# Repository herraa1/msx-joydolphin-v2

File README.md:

# Nintendo Gamecube controller adapter for MSX (msx-joydolphin) v2

Connect [Nintendo Gamecube controllers](https://en.wikipedia.org/wiki/GameCube_controller) to [MSX computers](https://www.msx.org/wiki/).

> [!NOTE]
>
> No build instructions are yet provided, but if you are brave enough go for the [recommended build](#recommended-build).
>

## Introduction

The msx-joydolphin v2 is an adapter that allows connecting Nintendo Gamecube controllers to [MSX general purpose I/O ports](https://www.msx.org/wiki/General_Purpose_port).

The main features of the msx-joydolphin v2 adapter are:
* small footprint
* made of widely available electronic components
* behaves as a cord extension between the MSX computer and the Nintendo Gamecube controller
* uses a female standard DE9 connector on the adapter's MSX joystick side
* uses a Gamecube Controller socket on the adapter's Nintendo Gamecube controller side
* no need for external power supply for wired controllers, the adapter draws current from the MSX port
* low power consumption for wired controllers (<20mA)
* serial debug provides information about the operation of the adapter
* supports WaveBird Wireless Controllers (which draw up to 150mA) when powering the adapter via USB

## Changes since v1

The msx-joydolphin v2 adapter now follows the behavior of the MSX joystick reference diagram of the MSX Technical Databook,
even when pin8 of the MSX general purpose I/O port is HIGH.
This makes the adapter now work seamlessly with MSX-HID, which required entering FM Towns compatibility mode
in msx-joydolphin v1.

## Adapter Name

Why msx-joydolphin?
The first part of the name is pretty obvious: _"msx"_ as this is an adapter for MSX computers and _"joy"_ as this is a joystick adapter.
The _"dolphin"_ part comes from the project codename assigned to the Nintendo Gamecube during its development.

## [Hardware](hardware/kicad/)

The msx-joydolphin v2 adapter uses an [Arduino Nano](https://store.arduino.cc/products/arduino-nano) to convert the [Nintendo Gamecube controller signalling](http://www.int03.co.uk/crema/hardware/gamecube/gc-control.html) to the [MSX joystick standard signalling](https://www.msx.org/wiki/Joystick_control).

A small printed circuit board (PCB) is used to easily bind all components:
* The Arduino Nano is connected using female headers (or soldered directly, when using the proposed the plastic case)
* PH2.0 connectors are used to connect cable extensions
* A 2.54 pitch debug header is added for convenience
* Through-hole components are used on the front side
* Surface mount device (SMD) components are used on the back side
  * The SMD components use footprints and sizes (1206) to make hand-soldering easier

Connection to the MSX general purpose I/O port is implemented using a DE9 joystick extension cable with a female DE9 connector on one side and a loose end on the other side.
The MSX joystick extension cable loose end is wired according to the following pinout mapping.

|  |
|:--|
| MSX joystick connector pinout, from controller plug side |

| MSX side pin | Cable color (may vary) | Signal | Arduino Nano side (port/pin/number) |
| ------------ | ---------------------- | ------ | ----------------------------------- |
| 5            | Brown                  | +5v    | _/5V/27                             |
| 4            | Orange                 | RIGHT  | PB3/D11/14                          |
| 3            | Grey                   | LEFT   | PB2/D10/13                          |
| 2            | Black                  | DOWN   | PB1/D9/12                           |
| 1            | Red                    | UP     | PB0/D8/11                           |
| 6            | Green                  | TRIGA  | PB4/D12/15                          |
| 7            | White                  | TRIGB  | PB5/D13/16                          |
| 8            | Blue                   | OUT    | PD2/D2/5                            |
| 9            | Yellow                 | GND    | _/GND/4,29                          |

The msx-joydolphin-v2 is fully compatible with MSX joysticks and honors the pin8 (OUT) signal.

The adapter uses open collector outputs (using 74LS03 Quad 2-Input NAND gates with open collector outputs) which makes the adapter safer [^3] than the
standard MSX joystick schematic depicted in the MSX Technical Data Book, as it avoids a series of undesired conditions that can lead to bus contention/short circuits.

Power is drawn from the +5V signal of the MSX general purpose I/O port, which is capable of delivering up to 50mA [^1].
The msx-joydolphin v2 draws below 20mA from the port when a wired controller is connected, so it is on the safe side. Anyway, the msx-joydolphin adapter uses a Positive Temperature Coeficient (PTC) resettable fuse of 50mA (F1) to limit current in case something goes wrong.

Also on the power side, a [1N5817 Schottky diode](https://www.onsemi.com/download/data-sheet/pdf/1n5817-d.pdf) (D1) is used to avoid leaking current from the msx-joydolphin adapter to the MSX in case the USB port of the Arduino Nano is connected to a computer or power supply while the adapter is plugged into an MSX.

Connection to the Nintendo Gamecube controller is done via a Nintendo Gamecube controller extension cable with a controller socket on one side and a loose end on the other side.
The Nintendo Gamecube controller extension cable loose end is wired according to the following pinout mapping.

|  |
|:--|
| Nintendo Gamecube connector pinout, from Nintendo Gamecube side |

| Gamecube socket pin | Cable color official | Cable color actual (may vary) | Signal | Comment                                                                   | Arduino Nano side (port/pin/number) |
| ------------------- | ---------------------| ----------------------------- | ------ | ------------------------------------------------------------------------- | ----------------------------------- |
| 1                   | Yellow               | White                         | +5v    | rumble, not used                                                          | N/C                                 |
| 2                   | Red                  | Red                           | DAT    | data line, uses 3v3 logic so it connects via a level shifter to PD7/D7/10 | \*( PD7/D7/10 )                     |
| 3                   | Green                | Black                         | GND    | ground                                                                    | _/GND/4,29                          |
| 4                   | White                | Blue                          | GND    | ground                                                                    | _/GND/4,29                          |
| 5                   |                      |                               |        |                                                                           | N/C                                 |
| 6                   | Blue                 | Green                         | 3.43v  | power line, 3v3                                                           | _/3v3/17                            |
| 7                   | Black                | N/A                           | GND    | ground                                                                    | N/C                                 |

The Nintendo Gamecube controller uses 3.3V for power and logic, except for the rumble motor which uses 5V.

Power for the Nintendo Gamecube controller is provided by the 3.3V pin of the FT232RL integrated in the Arduino Nano, which is capable of delivering up to 50mA [^2], enough to power a wired game controller.

As the Arduino Nano is a 5V logic microcontroller, the msx-joydolphin adapter uses a voltage level shifter based on the [BSS138 N-Channel Logic Level Enhancement Mode Field Effect Transistor](https://www.onsemi.com/pdf/datasheet/bss138-d.pdf) (Q1) to convert the Nintendo Gamecube controller DAT signal between 3.3V and 5V logic levels.

> [!WARNING]
> Do NOT connect the DAT line of the Nintendo Gamecube controller to the Arduino Nano directly, always use a voltage level shifter.
> The game controller may get damaged if you connect a 5V signal directly to the 3.3V DAT line.

If a WaveBird Wireless Controller is connected then the msx-joydolphin adapter needs to be powered via the mini USB port of the Arduino Nano, as the power consumption (150mA) is higher than what the MSX joystick port can deliver.
Althought it won't work, it is safe to connect a WaveBird Wireless Controller dongle without connecting an external USB power supply thanks to the current limitation of the PTC.
Also, connection of an external USB power supply to the Arduino Nano won't back-power the MSX computer thanks to the Schottky diode reverse current protection.

### Recommended Build

Please, use [msx-joydolphin-v2 Build1b](#build1b) for making new boards if you want something field-tested.

### [Build1b](hardware/kicad/msx-joydolphin-v2-Build1b)

[Bill Of Materials (BoM)](https://html-preview.github.io/?url=https://raw.githubusercontent.com/herraa1/msx-joydolphin-v2/main/hardware/kicad/msx-joydolphin-v2-Build1b/bom/ibom.html)

The Build1b adapter mimics completely the standard MSX joystick behaviour:

* When pin8 is HIGH, the adapter puts all stick and triggers signals in high impedance mode irrespective of their status (as if stick and triggers were not hold in the standard MSX joystick schematic), which become HIGH on the MSX side via the MSX PSG related circuitry pull-ups (matching the expected behavior)
* When pin8 is LOW
  * if a stick direction or trigger is hold, the corresponding signal is pulled down to GND causing it to be LOW (matching the expected behavior)
  * if a stick direction or trigger is not hold, the corresponding signal is put in high impedance mode, which becomes HIGH on the MSX side via the MSX PSG related circuitry pull-ups (matching the expected behaviour)

This build uses discrete logic components to honor the pin8 signaling (two [74LS03DR quad 2-input positive-nand gates with open collector outputs](https://www.ti.com/lit/ds/symlink/sn74ls03.pdf)) and uses open collector outputs which makes the adapter safer [^3] than the standard MSX joystick schematic depicted in the MSX Technical Data Book, as it avoids a series of undesired conditions that can lead to bus contention/short circuits.

||
|:--|
|msx-joydolphin-v2 Build1b first prototype unpopulated|

|||
|-|-|
|msx-joydolphin-v2 Build1b front populated|msx-joydolphin-v2 Build1b rear populated|

> [!NOTE]
> Do NOT populate resistor R3 as it is not needed.

## [Firmware](firmware/msx-joydolphin-v2/)

The msx-joydolphin v2 adapter firmware uses [NicoHood's Nintendo library](https://github.com/NicoHood/Nintendo) to read the Nintendo Gamecube controller status, and it is heavily inspired on [Daniel Jose Viana "Danjovic" firmware](https://github.com/Danjovic/MSX/blob/master/NSX-64) for a similar adapter for Nintendo 64 joysticks.

The following elements are used as inputs:
* digital pad (D-Pad), as direction arrows
* analog pad, as direction arrows
* A button, as Trigger 1
* B button, as Trigger 2

Those elements' status are processed by the msx-joydolphin firmware and transformed into MSX general purpose I/O port's signals on the fly.

## [Enclosure](enclosure/)

### Acrylic

A simple acrylic enclosure design for the project is provided to protect the electronic components and provide strain relief for the extension cords.

The enclosure uses a 3mm acrylic sheet.

The enclosure allows access to the USB port of the Arduino Nano without having to open it.

> [!NOTE]
> The height of the acrylic enclosure for msx-joydolphin-v2 has been reduced, so the Arduino Nano must be soldered in the same way as when using the plastic enclosure.

### Plastic

Another enclosure option is using an off-the-shelf [plastic case of 60x36x17mm](https://es.aliexpress.com/item/1005002139025547.html).

When using this option, the Arduino Nano must be soldered directly to the msx-joydolphin v2 board and its pin header legs must be trimmed down in order to fit within the reduced space of the case.

Also, you may need to trim a bit the pcb board corners with a file to slide the board into the case.

You can enlarge the existing hole on one of the case sides to access the mini USB connector, and make a new hole on the very left of the same side for the MSX joystick cable.

This way you can easily power the adapter via USB when you connect a Wavebird wireless controller.

You can use a plastic cover (a HDMI cover in this case) to protect the mini USB hole when not in use, as seen on the pictures.

## References

MSX general purpose I/O port
* https://www.msx.org/wiki/General_Purpose_port

Gamecube controller pinout
* https://allpinouts.org/pinouts/connectors/videogame/nintendo-gamecube-controller-connector-pinout/
* http://www.int03.co.uk/crema/hardware/gamecube/gc-control.html

Arduino Nano pinout
* https://content.arduino.cc/assets/Pinout-NANO_latest.pdf
* https://www.makerguides.com/arduino-nano/

Nico Hood Nintendo Gamecube Joystick arduino library
* https://github.com/NicoHood/Nintendo

Daniel Jose Viana "Danjovic" NSX-64 project
* https://github.com/Danjovic/MSX/blob/master/NSX-64

Gamecube controller IDs
* https://www.gc-forever.com/yagcd/chap9.html#sec9

[^1]: https://www.msx.org/wiki/General_Purpose_port
[^2]: https://www.mouser.es/datasheet/2/163/DS_FT232R-11534.pdf
[^3]: https://www.msx.org/wiki/Joystick/joypad_controller (see "Undesired Conditions")

## Image Sources

* https://www.oshwa.org/open-source-hardware-logo/
* https://consolemods.org/wiki/images/a/a1/GameCube_Controller_Pinout.svg
* https://en.wikipedia.org/wiki/File:Numbered_DE9_Diagram.svg
* https://commons.wikimedia.org/wiki/File:Video_Game_Controller_(56427)_-_The_Noun_Project.svg
* https://logo-timeline.fandom.com/wiki/GameCube?file=Nintendo_Dolphin_1999.svg

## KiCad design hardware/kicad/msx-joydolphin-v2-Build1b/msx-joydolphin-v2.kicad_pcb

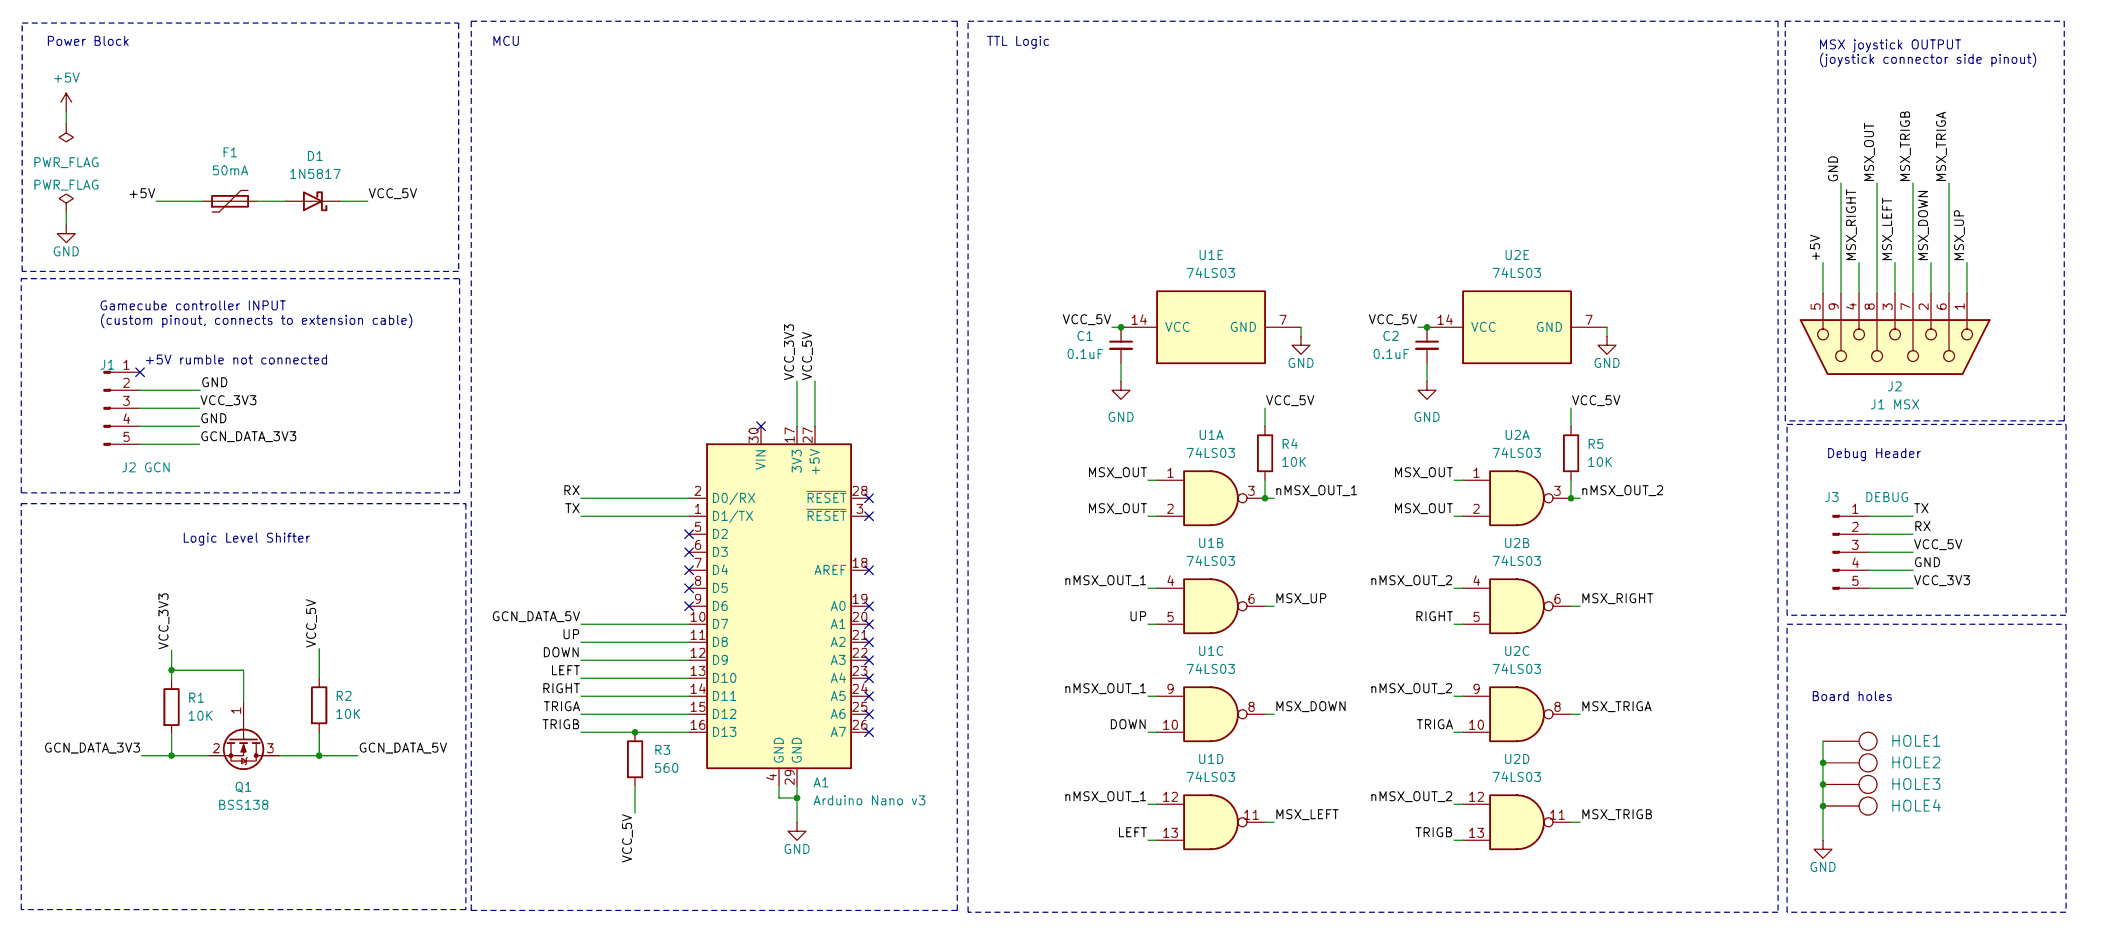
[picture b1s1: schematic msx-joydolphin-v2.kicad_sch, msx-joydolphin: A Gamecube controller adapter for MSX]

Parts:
A1: Arduino Nano v3; Arduino_Nano
C1, C2: 0.1uF; C_1206_3216Metric_Pad1.33x1.80mm_HandSolder
D1: 1N5817; D_DO-41_SOD81_P10.16mm_Horizontal
F1: 50mA; C_Disc_D7.5mm_W2.5mm_P5.00mm
HOLE1, HOLE2, HOLE3, HOLE4: HOLE; Hole_3mm
J1: J2 GCN; JST_PH_B5B-PH-K_1x05_P2.00mm_Vertical
J2: J1 MSX; JST_PH_B9B-PH-K_1x09_P2.00mm_Vertical
J3: DEBUG; Conn_Pin_Header_5x1_2.54mm
Q1: BSS138; SOT-23
R1, R2, R4, R5: 10K; R_1206_3216Metric_Pad1.30x1.75mm_HandSolder
R3: 560; R_1206_3216Metric_Pad1.30x1.75mm_HandSolder
U1, U2: 74LS03; SOIC-14_3.9x8.7mm_P1.27mm

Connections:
+5V: F1.1, J2.5
/DOWN: A1.12 (D9), U1.10
/GCN_DATA_3V3: J1.5, Q1.2 (S), R1.2
/GCN_DATA_5V: A1.10 (D7), Q1.3 (D), R2.2
/LEFT: A1.13 (D10), U1.13
/MSX_DOWN: J2.2, U1.8
/MSX_LEFT: J2.3, U1.11
/MSX_OUT: J2.8, U1.1, U1.2, U2.1, U2.2
/MSX_RIGHT: J2.4, U2.6
/MSX_TRIGA: J2.6, U2.8
/MSX_TRIGB: J2.7, U2.11
/MSX_UP: J2.1, U1.6
/RIGHT: A1.14 (D11), U2.5
/RX: A1.2 (D0/RX), J3.2
/TRIGA: A1.15 (D12), U2.10
/TRIGB: A1.16 (D13), R3.1, U2.13
/TX: A1.1 (D1/TX), J3.1
/UP: A1.11 (D8), U1.5
/VCC_3V3: A1.17 (3V3), J1.3, J3.5, Q1.1 (G), R1.1
/VCC_5V: A1.27 (+5V), C1.1, C2.1, D1.1 (K), J3.3, R2.1, R3.2, R4.1, R5.1, U1.14 (VCC), U2.14 (VCC)
/nMSX_OUT_1: R4.2, U1.3, U1.4, U1.9, U1.12
/nMSX_OUT_2: R5.2, U2.3, U2.4, U2.9, U2.12
GND: A1.4 (GND), A1.29 (GND), C1.2, C2.2, HOLE1.1, HOLE2.1, HOLE3.1, HOLE4.1, J1.2, J1.4, J2.9, J3.4, U1.7 (GND), U2.7 (GND)
unnamed: D1.2 (A), F1.2

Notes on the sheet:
Power Block
Debug Header
TTL Logic
+5V rumble not connected
MCU
Board holes
Logic Level Shifter
MSX joystick OUTPUT (joystick connector side pinout)
Gamecube controller INPUT (custom pinout, connects to extension cable)

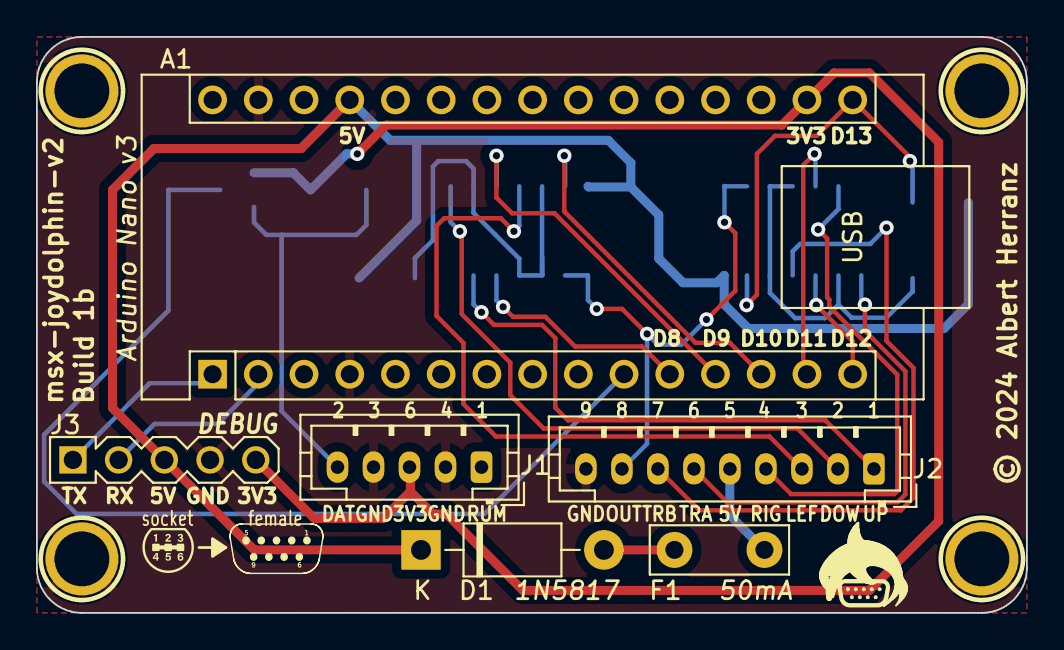
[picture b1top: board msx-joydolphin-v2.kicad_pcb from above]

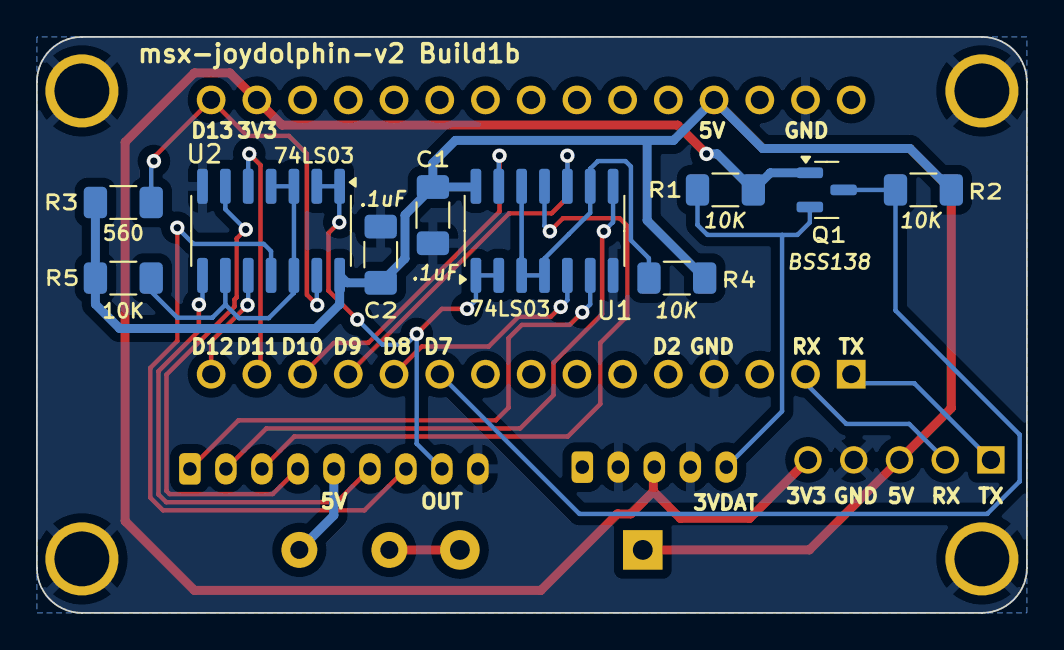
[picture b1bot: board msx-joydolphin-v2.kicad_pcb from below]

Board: 2 copper layers, 55.0 x 32.0 mm, 20 parts (10 on the bottom side), 24 nets.

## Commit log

2024-04-08 Initial commit.
2024-04-20 v2-build1c: prototype built
2024-04-22 readme: small fix
2024-04-27 acrylic enclosure updated
2024-05-03 readme: linkify build1b section
2024-12-25 readme: no build instructions yet

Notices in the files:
hardware/kicad/msx-joydolphin-v2-Build1b/msx-joydolphin-v2.kicad_pcb:
© 2024 Albert Herranz
